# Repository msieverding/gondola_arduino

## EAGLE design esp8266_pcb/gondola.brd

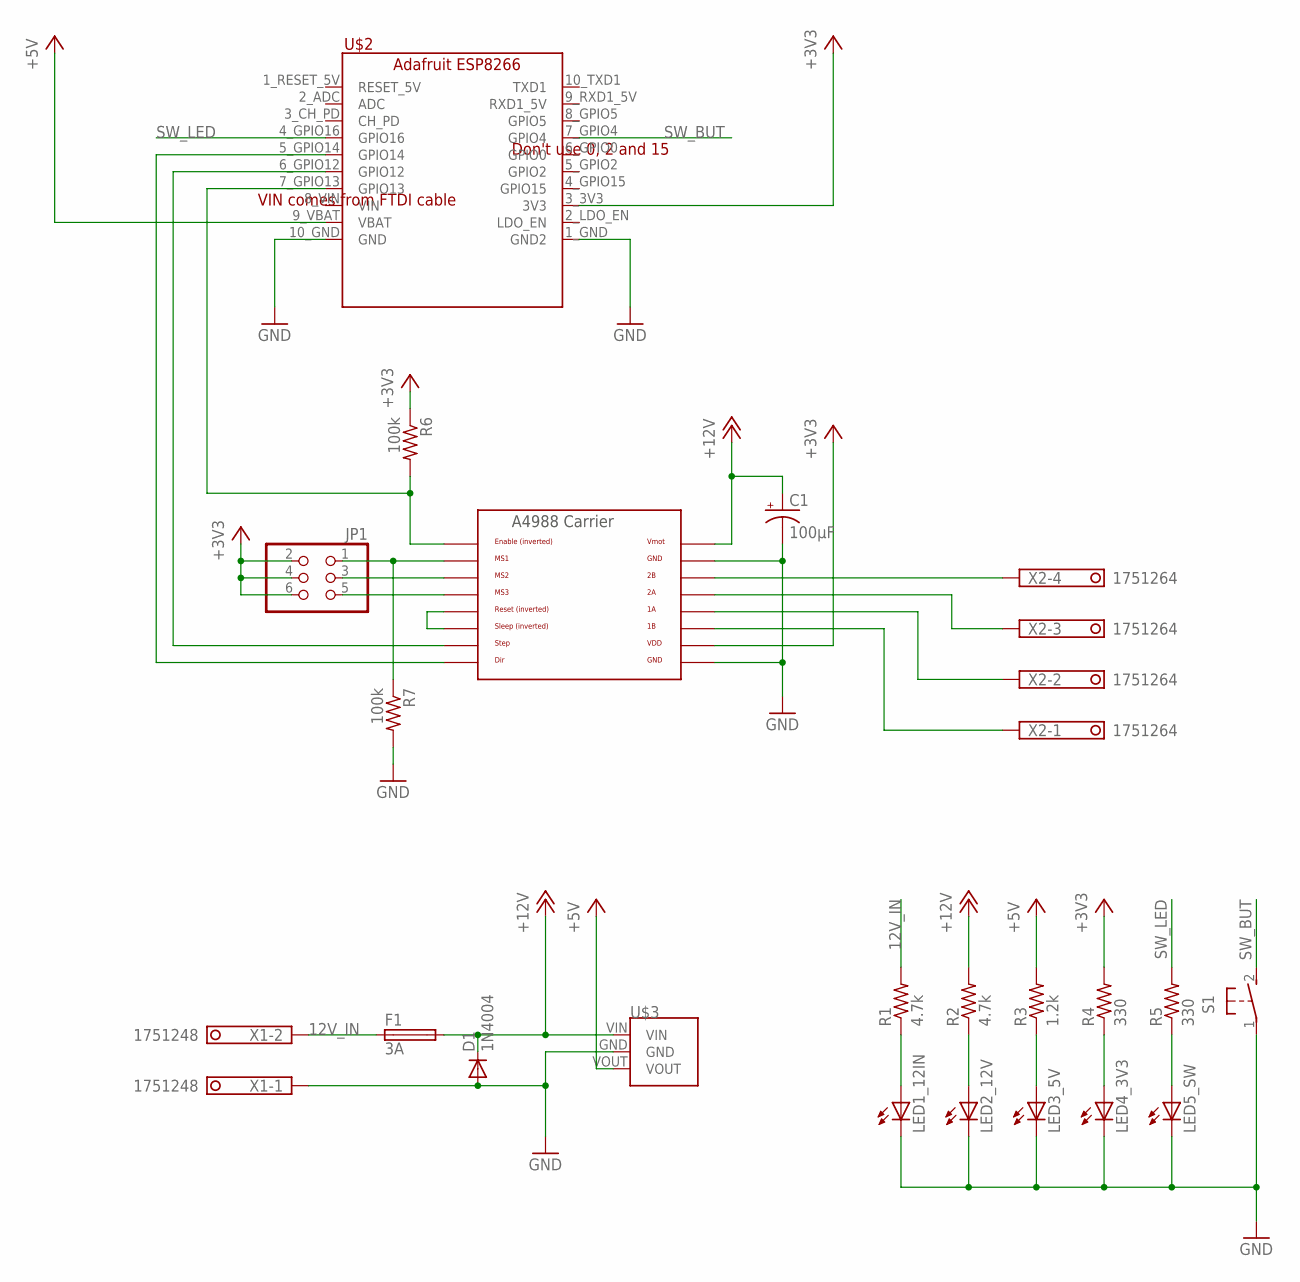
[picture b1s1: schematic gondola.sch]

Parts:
C1: 100µF; 153CLV-0605
D1: 1N4004; DO41-10
F1: 3A; LITTLEFUSE
JP1: PINHD-2X3; 2X03
LED1_12IN, LED2_12V, LED3_5V, LED4_3V3, LED5_SW: LEDCHIP-LED0805; CHIP-LED0805
R1, R2: 4.7k; R0805
R3: 1.2k; R0805
R4, R5: 330; R0805
R6, R7: 100k; R0805
S1: 31-XX; B3F-31XX
U$1: A4988BREAKOUT
U$2: ADAFRUIT_ESP8266
U$3: ROHM_BP5293-XX
X1: 1751248
X2: 1751264

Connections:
1A: U$1.1A, X2.2
1B: U$1.1B, X2.1
2A: U$1.2A, X2.3
2B: U$1.2B, X2.4
12V_IN: F1.1, R1.2, X1.2
!RESET: U$1.RST, U$1.SLP (SLEEP)
+3V3: JP1.2, JP1.4, JP1.6, R4.2, R6.1, U$1.VDD, U$2.3_3V3 (3V3)
+5V: R3.2, U$2.9_VBAT (VBAT), U$3.VOUT
+12V: C1.+, D1.C, F1.2, R2.2, U$1.VMOT, U$3.VIN
DIR: U$1.DIR, U$2.5_GPIO14 (GPIO14)
GND: C1.-, D1.A, LED1_12IN.C, LED2_12V.C, LED3_5V.C, LED4_3V3.C, LED5_SW.C, R7.2, S1.1, U$1.GND, U$1.GND@0 (GND), U$2.1_GND (GND2), U$2.10_GND (GND), U$3.GND, X1.1
MS1: JP1.1, R7.1, U$1.MS1
MS2: JP1.3, U$1.MS2
MS3: JP1.5, U$1.MS3
M_EN: R6.2, U$1.EN, U$2.7_GPIO13 (GPIO13)
unnamed: LED2_12V.A, R2.1
unnamed: LED1_12IN.A, R1.1
unnamed: LED4_3V3.A, R4.1
unnamed: LED5_SW.A, R5.1
unnamed: LED3_5V.A, R3.1
STEP: U$1.STEP, U$2.6_GPIO12 (GPIO12)
SW_BUT: S1.2 (S), U$2.7_GPIO4 (GPIO4)
SW_LED: R5.2, U$2.4_GPIO16 (GPIO16)

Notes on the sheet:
Don't use 0, 2 and 15
VIN comes from FTDI cable

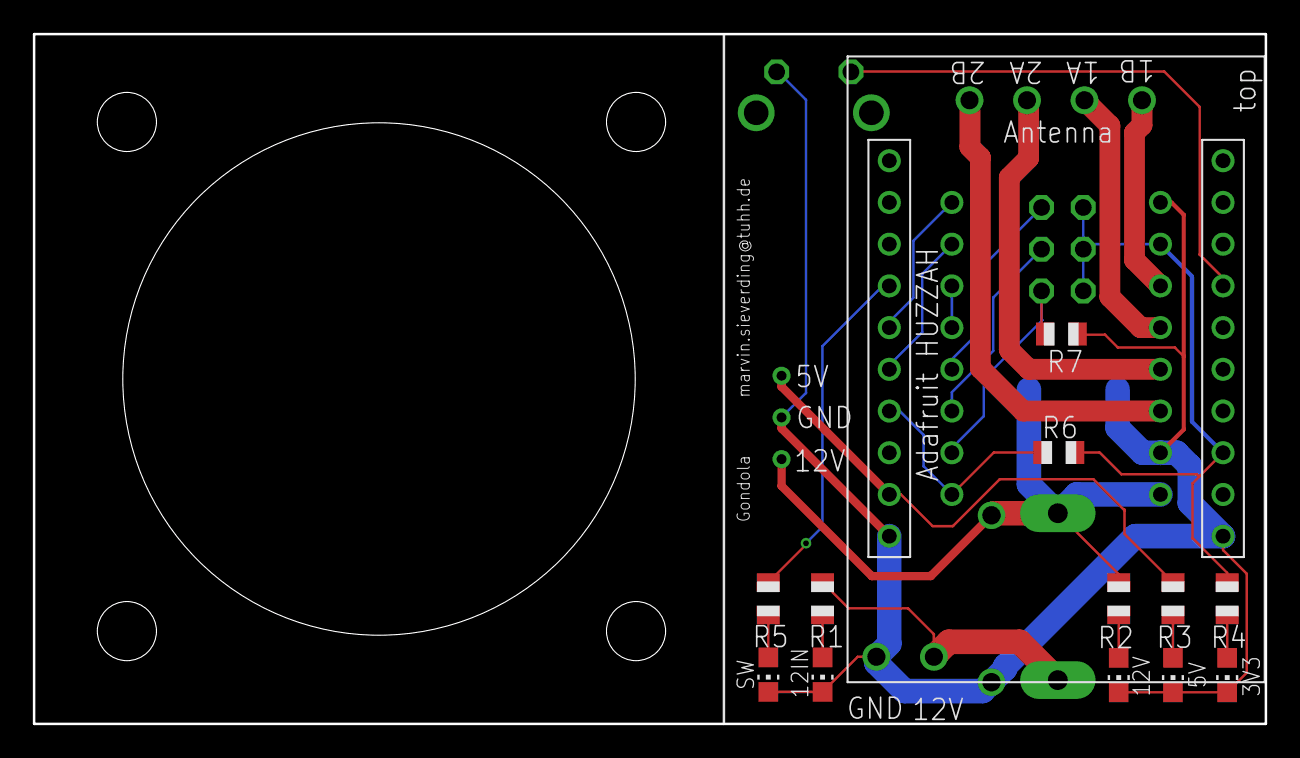
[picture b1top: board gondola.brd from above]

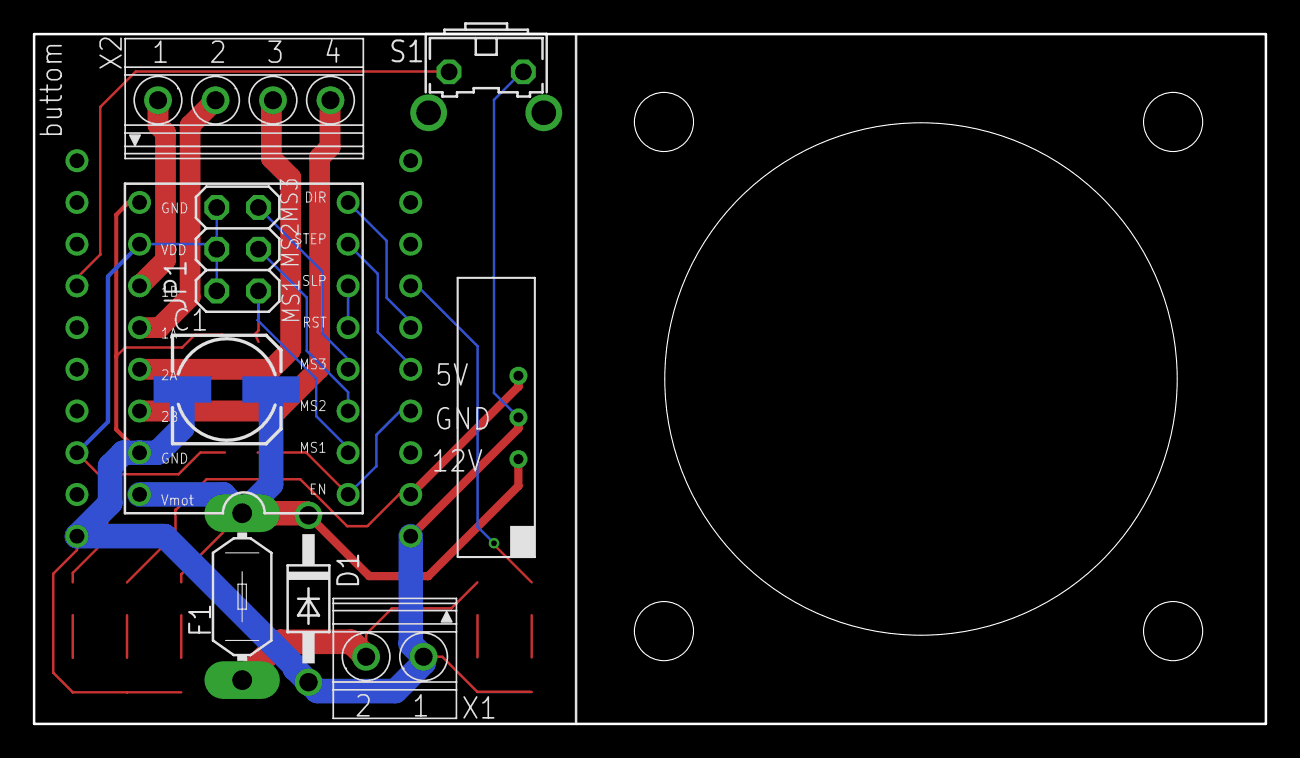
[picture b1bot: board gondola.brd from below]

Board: 2 copper layers, 75.0 x 42.0 mm, 22 parts (9 on the bottom side), 23 nets.

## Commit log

2017-08-02 code formatting
2017-08-02 add atom build environment
2017-08-04 add implementation of first wifi client as reference setup
2017-08-04 changed implementation to file distributed cpp
2017-08-04 changed wifi server implementation to the new distributed cpp files
2017-08-04 some work on wifi client main
2017-08-04 added all files for a WiFi access point
2017-08-04 first working web interface
2017-08-08 first Class for connection and for the httpServer
2017-08-08 added move request
2017-08-08 embedded anchors to gondola
2017-08-08 renamed class files to first letter uppercase
2017-08-08 embedded movement to webserver
2017-08-08 added Interface for the connection
2017-08-08 added Serial connection as IConnection
2017-08-08 added AP connection as IConnection
2017-08-08 add MDNS for wifi connection
2017-08-08 add mode for AP WiFi
2017-08-08 aded check for valid arguments in WebServer
2017-08-08 delted and renamend some files. WiFi AP is now located in the same project as WiFi Client
2017-08-08 updared TODO file & small changes
2017-08-08 added implementation of lists and command interpreter
2017-08-08 fixed bug in lists + destructors
2017-08-08 first implementation of contype command. Debugging output in contypeCommand still active
2017-08-09 fixed bugs in serial readout and some nice functions for commandInterpreter
2017-08-09 some layout of serial printout
2017-08-15 changed todo language
2017-08-16 repair file Gondola.cpp
2017-08-16 calculated missing spooling time
2017-08-17 added ConnectionMgr -> Connection change through webserver works
2017-08-18 [Config][WebPage] Added Config Class with WiFi-parameter, get and set methods Some work on setupWiFi and Move WebPage
2017-08-18 [WebServer] Set initial position of gondola through browser
2017-08-20 [Config] saved configuration in EEPROM
2017-08-20 [WiFiConnection] Added DHCP / static IP functionality
2017-08-20 [Gondola] minor change in movement function
2017-08-20 [Connection] maked Connections as singletons to access them via the command line interpreter
2017-08-20 [Documentation] Documentet all classes
2017-08-20 [Config] Reset command
2017-08-20 [Config]Typo in EEPROM address [Log]Reduced debug output
2017-08-20 [Log]Add Logging class with 3 different log levels
2017-08-20 [WiFiConnection] activated mDNS. Software on other host was missing... See comment of setupMDNS function
2017-08-21 Update README.md
    Changed from arduino to esp8266
2017-08-21 Update README.md
    some details
2017-08-24 [DualConnection] Added a connection type for an access point and a normal WiFi Connection at one time
2017-08-24 [Anchor] added HardwareAnchor as a heritage of interface IAnchor
2017-08-24 [WebServer]Divided WebServer up into 3 different webServers -> normal(parent class), Master and Slave [Gondola]Gondola is now a singleton
2017-08-24 [WebServer] First tested version of Master/Slave system [Anchor] Major changes in class specification
2017-08-24 [WebServer] More work on the webserver [Documentaton] Added more documentation
2017-08-24 [WebServerMaster] Added destructor [Gondola] Added list deletion in destructor
2017-08-24 [Compilation]Fixed warnings
2017-08-25 [Config] Added fletcher checksum for EEPROM data
2017-09-04 [APConnection] added WiFi settings (mode and signal strength)
2017-09-04 [WebServer]Fixed typo in webserver handleSetupSystem
2017-09-04 [WebServerMaster][WebServerSlave] Fixed registration at master
2017-09-04 debugging
2017-09-04 [WiFiConnection]Set Hostname before WiFi.begin() for correct DNS entries
2017-09-05 [APConnection] Fixed bug that APConnecton deos not work
    DNSServer of APConnection was not handled and this disturbed the access point
2017-09-05 [Config] Removed static variables
2017-09-05 [WiFiConnection] Fixed issue with mDNS
2017-09-05 add library for MqTT Server
2017-09-05 first test
2017-09-05 first working MqTT implementation
2017-09-06 MQTTServer and MQTTClient as heritage of IConnection
2017-09-06 [MqTTlib]reduced MqTT implementation. EEPROM access through own config now
2017-09-06 [MqTTlib] improved cding style of MqTTlib
2017-09-06 [MqTTlib] Some fixes for MQTTClient. Basicly works now
2017-09-06 [MQTTServer] MqTT Server publishes a test broadcast
2017-09-06 introduced IMQTTService as superclass for the MqTT Server and Client
2017-09-07 [MqTTlib] some addition to last commit
2017-09-07 [MqTTlib] stripped MqTTlib
2017-09-07 [Gondola][Anchor][MqTTServer] MqTTServer heritates from interface IGondola
2017-09-08 Some Gondoala and movement implementations
2017-09-08 [Gondola] Connection of Gondola and Anchor to the other classes
2017-09-08 [Framework] Framework improvements
2017-09-08 [Config] Print config on startup when log level is at least LOG_DEBUG
2017-09-08 [Config]Chip should not crash anymore after a config reset
2017-09-08 [MqTT] Renamed a member of MQTTClient
2017-09-08 [MqTT] Added asynchronous MqTT client
2017-09-11 [Framework] + [MqTT]implemented moveCommand with strings due to missing binary support of MqTT broker library
2017-09-11 [ConnectionMgr][Config]No manual reset necessary anymore!
2017-09-11 [MqTTClient]Added cyclic anchor status message
2017-09-11 [CommandInterpreter]Feedback after command (Success/Fail)
2017-09-13 first ping tests with WebSockets
2017-09-13 [CommandInterpreter] Fix for the delete function
    The content of the iterator would be deleted with list.delete(it). Than it++ wouldn't work anymore. So the iterator must be incremented and than the old iterator should be deleted
2017-09-13 [CommandInterpreter] Ignore simple 'Return' presses of the user into the serial console and don't write a warning into the console
2017-09-13 First move implementation with WebSockets
2017-09-14 Some more work on gondolas movement
2017-09-15 Correct anchor movement and made documentation
2017-09-15 [WebServer] Auto reload while movement
2017-09-15 Fixed some bugs during first 2D testing
2017-09-16 some small changes on documentation and updated class diagram
2017-09-18 added graph for WSO_MESSAGES
    +
    push new (remote) anchors to the front, so that the hardware anchor starts to spool after the message to the remote anchors was delivered (better synchronisation during spooling)
2017-09-18 [WebSockets]Added timeout detection
2017-09-18 [WebServer] Show registered anchors on main page
2017-09-18 [Anchor] Fixed bug, that motor made one step too much
2017-09-20 changed model of anchors
2017-09-20 fixed some bugs
2017-09-22 Some improvements, bugfixes and software error corrections
2017-09-22 deleted rope length from code
2017-09-22 changed some small things in the configuration
2017-09-22 [WebSocket] Asynchronous web sockets with compiler flag
2017-09-23 [Log] Add Website with log information
2017-09-26 change rounding of targetSpooledDistance
2017-09-26 updated class diagramm
2017-09-27 updated code documentation
2017-09-27 added eagle files of PCB
2017-10-06 some work on pcb
